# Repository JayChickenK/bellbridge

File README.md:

# BellBridge

**An isolated ESP32-C6 board that brings a Ritto 7630 TwinBus apartment intercom into Home Assistant.**

BellBridge connects to four terminals of the indoor station. It tells the
**apartment bell** from the **street bell** and can **open the street door**, all
locally through [ESPHome](https://esphome.io/) with no cloud involved. It is the circuit of
[duramson/ritto-esp](https://github.com/duramson/ritto-esp) turned into a
27.5 × 22.8 mm board that PCBWay assembles completely, ESP32-C6 module included.

<!-- TODO after testing: replace the status line, e.g.
> **Status:** v2.0 built and tested on a Ritto 7630 (YYYY-MM-DD), see the [test report](docs/testing.md).
-->
> [!WARNING]
> **Status:** hardware v2.0 is designed and checked, but it has not yet been built or
> tested on an intercom. It is v1.15 turned for mounting in the Ritto 7630: antenna up,
> USB-C and the screw terminal side by side on the bottom edge, with smaller parts (TLP293
> optocouplers, 0402 resistors and capacitors). Same circuit and GPIOs; see the
> [changelog](CHANGELOG.md).

<!-- TODO: add photos, e.g.

-->

The assembled board as a KiCad render, looking at its bottom edge: USB-C and the screw
terminal side by side in front, the module behind them with its antenna sticking out
5.2 mm past the far (top) edge.
The USB-C receptacle and the screw terminal are simplified models drawn to their
datasheet dimensions; the other parts use the 3D models from KiCad's and Espressif's
libraries.

| Top (render) | Bottom (render) |
| --- | --- |
|  |  |

These two renders show the bare board, pads and silkscreen without the parts.

## Features

- **Two bells told apart:** the chime line pulses on every ring, and the floor line drops
  only on an apartment ring. The firmware combines the two into "Doorbell Main" and
  "Doorbell Apartment".
- **Door opener:** an "Open Door" button in Home Assistant pulls the opener line to bus
  ground for 0.5 s (adjustable). An optional "Auto Open" switch lets every street ring
  open the door while it is on, for expected guests; it turns itself off after an
  adjustable time (30 minutes by default) and on every restart.
- **Galvanic isolation:** all three lines go through optocouplers. Bus ground and USB
  ground are kept apart by a 1.6 mm copper-free strip on both layers.
- **Powered from USB-C (5 V), not from the bus.** USB ESD protection right in the D+/D−
  path, 3.3 V LDO.
- **ESP32-C6-MINI-1-N4:** Wi-Fi 6 with a PCB antenna, an encrypted Home Assistant API,
  password-protected OTA updates, and diagnostics (signal, uptime, chip temperature, IP
  address).
- **Fully assembled by PCBWay.** The screw terminal is the only through-hole part.
- **Drop-in for ritto-esp:** same terminal order, same ESPHome node and entity names,
  so existing automations keep working.

## How it works

The Ritto 7630 shares one two-wire TwinBus with both door stations and all flats.
[ritto-esp](https://github.com/duramson/ritto-esp#reverse-engineering-the-bus) measured the
board with an oscilloscope:

| Ritto terminal | Signal | Behaviour |
| --- | --- | --- |
| 2 KLINGEL (chime) | input | about 5 V for ~500 ms on **any** ring |
| 4 ETAGE (floor) | input | idles at about 5 V, **drops to ground** while the apartment button is pressed |
| 5 door opener | output | buzzes the street door when **pulled to ground** |
| 1 / 6 GND | ground | bus ground |
| 3 +24 V | — | bus supply, **never connected to BellBridge** |

A falling ETAGE line means "apartment bell". The chime pulse that follows about 1.6 s later
is blocked for a few seconds, so a chime pulse on its own means "street door".

## Hardware at a glance

| | |
| --- | --- |
| Size | 27.5 × 22.8 mm, 2 layers, 1.6 mm, no mounting holes; 27.5 × 28.0 mm with the module's antenna, which sticks out past the top edge |
| Connectors | USB-C and the screw terminal side by side on the bottom edge; both cables leave downward |
| Tallest part | screw terminal J1, 8.4 mm; then the USB-C receptacle, 3.3 mm, and the module, 2.4 mm |
| Controller | Espressif ESP32-C6-MINI-1-N4 (4 MB flash, PCB antenna) |
| Power | USB-C, 5 V; AP2112K-3.3 LDO; USBLC6-2P6 ESD protection |
| Inputs | CHIME and FLOOR, 1.5 kΩ / 0.5 W into TLP293 optocouplers (about 2.5 mA at 5 V) |
| Output | DOOR, TLP293 transistor to bus ground |
| Isolation | separate grounds, 1.6 mm copper-free barrier, 5.1 mm between the optocouplers' input and output pads, 3,750 V<sub>rms</sub> optocouplers |
| Terminal | DORABO DB125-2.54, 4 pins at 2.54 mm: DOOR, CHIME, FLOOR, GND |

Details, the parts list and the design checks are in [hardware/README.md](hardware/README.md).

## Versions

| | v2.0 (current) | [v1.15](https://github.com/JayChickenK/bellbridge/tree/v1.15), [v1.14](https://github.com/JayChickenK/bellbridge/tree/v1.14), [v1.13](https://github.com/JayChickenK/bellbridge/tree/v1.13), [v1.12](https://github.com/JayChickenK/bellbridge/tree/v1.12) and [v1.1](https://github.com/JayChickenK/bellbridge/tree/v1.1) | [v1.0](https://github.com/JayChickenK/bellbridge/tree/v1.0) |
| --- | --- | --- | --- |
| Board | 27.5 × 22.8 mm; 28.0 mm tall with the antenna | 26.2 × 27.5 mm; 31.4 mm wide with the antenna | 36.4 × 31.5 mm |
| Antenna | past the top edge, as Espressif recommends | past the left edge, as Espressif recommends | on the board, at its edge |
| USB-C | bottom edge, beside the terminal; HRO's recommended land | top edge, HRO's recommended land | left edge, KiCad's land |
| Terminal | bottom edge, wires leave downward; DORABO, 2.54 mm, 26–18 AWG | right edge; DORABO, 2.54 mm, 26–18 AWG | KANGNEX, 3.81 mm, 26–16 AWG |
| USB ESD array | USBLC6-2P6 in the D+/D− path | USBLC6-2P6 in the D+/D− path | USBLC6-2SC6 on side branches |
| Optocouplers | TLP293 (SO4, 1.27 mm pitch) | LTV-357T (SO-4) | LTV-817S (SMDIP-4) with a milled slot |
| Passives | 0402, the 10/22 µF capacitors 0603; R2/R3 in 0805, 0.5 W | 0603; R2/R3 in 1210, 0.5 W | 0805; R2/R3 in 2512, 1 W |
| Download mode, reset | test pads on the back, replug USB | test pads on the back, replug USB | BOOT and RESET buttons |

v1.12 is v1.1 with three part values changed (R6 10 kΩ, C6 10 µF, C2 22 µF) and a wider
panel note for PCBWay; the copper is the same. v1.13 adds tracks for the bus ground, so it no
longer depends on the ground pour alone; v1.14 prints the terminal labels with thicker
lines, and v1.15 has smoother tracks, redrawn by hand in KiCad. v2.0 turns the layout for
mounting in the Ritto 7630, with both cables leaving at the bottom, and uses smaller parts
(TLP293 optocouplers, 0402 resistors and capacitors). All versions have the
same circuit,
terminal order and GPIOs. v1.0 has been assembled (photos below); the later versions have
not been built yet. The firmware in this branch runs on
all of them; the copy in the v1.0 files has a bell-logic bug (see the
[changelog](CHANGELOG.md)). Each version's order files are attached to its
[release](https://github.com/JayChickenK/bellbridge/releases).

| BellBridge v1.0, assembled | BellBridge v1.0, assembled (angled view) |
| --- | --- |
|  |  |

## Wiring

| BellBridge J1 | Ritto 7630 terminal |
| --- | --- |
| DOOR | 5 (door opener) |
| CHIME | 2 (KLINGEL) |
| FLOOR | 4 (ETAGE) |
| GND | 1 or 6 (GND) |
| — | 3 (+24 V) stays unconnected |

See [docs/installation.md](docs/installation.md) before you open the intercom.

## Getting started

1. **Order** the assembled board: [docs/ordering.md](docs/ordering.md).
2. **Flash** the firmware over USB-C: [firmware/README.md](firmware/README.md).
3. **Test** it on the bench: [docs/testing.md](docs/testing.md).
4. **Install** it at the intercom: [docs/installation.md](docs/installation.md).
5. **Automate** in Home Assistant. The
   [ritto-esp automations](https://github.com/duramson/ritto-esp/tree/main/home-assistant)
   (notifications, parcel mode, personal door webhooks) work unchanged.

## Test results

<!-- TODO after testing: fill in from docs/testing.md -->

| Test | Result |
| --- | --- |
| Assembly inspection, isolation, 3.3 V rail | not yet tested |
| Flashing over USB-C, Wi-Fi signal | not yet tested |
| Bench test of CHIME, FLOOR and DOOR | not yet tested |
| Street bell, apartment bell, door opener on a Ritto 7630 | not yet tested |
| Long-term run without false triggers | not yet tested |

## Repository layout

```
hardware/    board generator (generate.py), KiCad board, BOM, CPL, PCBWay order files
firmware/    ESPHome configuration and secrets template
docs/        ordering, installation and test guides, images
```

## Credits

- [duramson/ritto-esp](https://github.com/duramson/ritto-esp): reverse engineering of the
  7630, the circuit and the ESPHome firmware this board is built on (MIT License).
- [deh0511.de TwinBus](https://deh0511.de/twinbus/) and
  [quhfan.de](https://quhfan.de/post/ritto-twinbus-7630-smart-home-assistant/): terminal
  pinout of the 7630.

## License

[MIT](LICENSE). The firmware is derived from ritto-esp, whose MIT notice is kept in
[LICENSE](LICENSE) and in the firmware file.

Ritto and TwinBus are trademarks of their respective owners. This project is not
affiliated with or endorsed by them. You build and install it at your own risk. In a rented
flat, the intercom usually belongs to the building, so ask before you modify it.

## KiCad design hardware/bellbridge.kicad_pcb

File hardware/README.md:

# BellBridge hardware (v2.0)

[`generate.py`](generate.py) places and routes every part, checks the result, and writes the
KiCad board and the PCBWay order files. For v2.0 the tracks of every net but VBUS were routed
by `generate.py` and then smoothed in the style of the tracks redrawn by hand for v1.15
(45° corners, no stair steps); [`hand_routes.json`](hand_routes.json) holds them, and
`generate.py` lays them down instead of its own routes for those nets. To change the board,
change the script or `hand_routes.json` and run it again (see [Regenerating](#regenerating));
edits made only in KiCad are overwritten by the next run.

## Overview

- **27.5 × 22.8 mm** board, 2 layers, 1.6 mm FR-4, no mounting holes; with the module's
  antenna sticking out past the top edge, 27.5 × 28.0 mm overall. Laid out for mounting in
  the Ritto 7630: antenna up, both cables leave at the bottom. v1.15 was 26.2 × 27.5 mm
  with the antenna to the left, v1.0 36.4 × 31.5 mm; [CHANGELOG.md](../CHANGELOG.md) lists
  what changed.
- **ESP32-C6-MINI-1-N4** module with PCB antenna, soldered by the assembler (not a plug-in
  XIAO board). It stands upright: its antenna sticks out 5.2 mm past the top edge.
- **USB-C** at the bottom edge, below the module, opening downward. As in HRO's drawing, the
  receptacle front sits 0.46 mm past the board edge.
- **Screw terminal J1** at the bottom edge, right of USB-C. Its wire openings face downward
  and the body overhangs the edge by 0.9 mm. At 8.4 mm, J1 is the tallest part; the module
  is about 2.4 mm.
- **Two grounds:** `GND_MCU` (USB, module) and `GND_BUS` (intercom) are never joined. An
  L-shaped 1.6 mm copper-free barrier on both layers separates all copper of the two sides,
  ground pours included. The optocouplers stand across it.
- **+24 V is not connected.** There is no pad and no net for it.

```
USB-C ─ USBLC6-2P6 ─ ESP32-C6-MINI-1        D+/D− run through U3 to the module
  └─ VBUS ─ AP2112K-3.3 ─ 3V3 ┘
                                     │ GPIO19     │ GPIO18     │ GPIO20
                                    OK1 (LED)    OK2 (photo)  OK3 (photo)
 GND_MCU   ════════════════ isolation barrier, 1.6 mm ═════════════════
 GND_BUS                            OK1 (photo)  OK2 (LED)    OK3 (LED)
                                     │            │ 1.5 kΩ     │ 1.5 kΩ
                                    DOOR         CHIME        FLOOR       GND
                                    └──────── J1, to the Ritto 7630 ────────┘
```

## Signals

| J1, right to left (top view) | Function | Direction | Module GPIO |
| --- | --- | --- | --- |
| DOOR | door opener (Ritto terminal 5) | output, OK1 pulls it to `GND_BUS` | GPIO19 |
| CHIME | chime, any ring (Ritto terminal 2, KLINGEL) | input | GPIO18 |
| FLOOR | apartment bell (Ritto terminal 4, ETAGE) | input | GPIO20 |
| GND | bus ground (Ritto terminal 1 or 6) | — | — |

**Inputs (OK2, OK3).** The LED sits on the bus side behind 1.5 kΩ. ritto-esp measured CHIME
and FLOOR at about 5 V (the scope traces top out around 4.8 V). That gives about 2.4 mA of
LED current, or 2.5 mA at a full 5 V. The 10 kΩ pull-ups (R4, R5) need 0.33 mA, far less
than the transistor sinks at that LED current: the TLP293's rank GB guarantees a CTR of
100–600 % at 0.5 mA as well as at 5 mA (Toshiba datasheet, table 8.1). The 1.5 kΩ resistors
(R2, R3) are Panasonic ERJ-P06F1501V, anti-surge thick-film parts in 0805 rated 0.5 W at
70 °C (derated linearly to zero at 155 °C; 27 V continuous at 1.5 kΩ), because Ritto
terminal 3 (+24 V) sits between KLINGEL and ETAGE. If a wire lands there by mistake, 15 mA
flows and each resistor takes 22.8 V and dissipates about 0.35 W, which the derating curve
allows up to about 95 °C ambient. A standard 0805 resistor (0.125 W) would not survive
that; KOA's SG73P2ATTD1501F (0805, rated 0.75 W at 70 °C) may replace the Panasonic part.
This covers a CHIME or FLOOR wire on +24 V, not the GND wire: with J1's GND on +24 V, the
LEDs of OK2 and OK3 would be driven backward (rated 5 V) and OK1's output from emitter to
collector (rated 7 V).

**Output (OK1).** GPIO19 drives the LED through 150 Ω (about 12 mA). The collector is on
DOOR and the emitter on `GND_BUS`, so the transistor pulls the opener line to bus ground.
The TLP293 is rated V<sub>CEO</sub> 80 V and 50 mA collector current. Rank GB guarantees 100
% CTR at I<sub>F</sub> = 5 mA, and Toshiba's CTR curve stays flat up to about 20 mA, so the
output sinks about 12 mA or more, typically about 24 mA (the LTV-357T-C of earlier versions:
rank C, 200 % at 5 mA, about 19 mA at 220 Ω). R6 (10 kΩ to ground) holds GPIO19 low from
reset until the firmware drives it, so the door does not buzz while the module boots. Only
while the chip itself is held in reset is the pin's weak internal pull-up on (ESP32-C6 IO
MUX table, GPIO19 = SDIO_CLK); against 10 kΩ it lifts the pin to only about 0.6 V, below the
LED's forward voltage, so OK1 stays off. While the firmware switches the LED on (12 mA), R6
draws another 0.33 mA.

**Straps and test pads.** GPIO8 and GPIO9 are strapping pins. GPIO8 has a 10 kΩ pull-up
(R12); GPIO9 relies on the module's internal pull-up, as in the MINI-1 datasheet's
peripheral schematic (figure 7: GPIO9 only goes to a jumper to ground). Espressif's chip
design guide recommends an external pull-up on GPIO9; one would not fit beside the module's
GPIO9 pin in the v1.1 layout, and v2.0 keeps the circuit. There are no buttons: `esptool`
puts the module into download mode over the USB serial/JTAG port, and replugging USB resets
it. If a broken firmware stops that from working, bridge the two bare pads on the back, TP1
(BOOT, GPIO9) and TP2 (GND), with tweezers while you plug in USB; the module then starts in
download mode. The test pads sit on the back, under the module's lower right corner near its
GPIO9 pin. No 3V3 or VBUS copper comes within 1 mm of them (3V3 is 1.3 mm from TP2), so a
slip of the tweezers cannot short the supply to ground; the nearest other copper is GPIO18's
tented via, 0.7 mm from TP1, an input that a slip cannot harm. EN has 10 kΩ (R8) and
10 µF (C6, the same part as C1 and C3), which holds the chip in reset for about 0.1 s after
power-up; Espressif gives 10 kΩ + 1 µF as values to adjust to the power-up timing. Pin 8 is
on the module's left side, right beside R8 and C6, so EN reaches them over 2.4 and 3.6 mm of
track on the front, without a via. GPIO15 stays open.

**Firmware.** The firmware uses the three GPIOs directly. The XIAO ESP32-C6 antenna switch
(GPIO3, GPIO14) does not exist here, so do not use the `seeed_xiao_esp32c6` board profile;
see [../firmware](../firmware/).

## Power

USB-C only, 5 V, with all four VBUS contacts connected. CC1 and CC2 each have 5.1 kΩ to
ground (R7, R10); SBU1/SBU2 stay open.

U3 (USBLC6-2P6) sits in the D+/D− path between the receptacle and the module, 2.7–5.2 mm
of track from the receptacle's pads and 2.2–3.0 mm from the module's pins (distances in
this section run along the copper from pad centre to pad centre). D+ runs through U3's
pin 1, and D− taps pin 4 with a 0.6 mm stub. Both lines stay on the front and run straight
up into the module's pins 18 and 17, 5.6–8.1 mm from the receptacle's pads, so a discharge
into the receptacle meets U3 before it reaches the module. U3's ground pin has its own via
0.85 mm away. Its VBUS pin and C7 (100 nF to ground) sit on one line, 1.65 mm apart, as in
the layout figure of ST's USBLC6-2 datasheet; VBUS arrives through a via between the two,
and C7's ground pad shares the via under module pin 14 (1.3 mm of track). CC1 runs from
its receptacle pad to R7 on the front, below C7, without a via.

The AP2112K-3.3 (600 mA, stable with ceramic capacitors) makes 3.3 V; its EN is tied to
VBUS. Capacitors: 10 µF + 100 nF at the input (C1, C4; 3.2 mm and 2.4 mm of track from
VIN), 10 µF at the output (C3, 3.0 mm from VOUT), and 100 nF + 22 µF at module pin 3 (C5,
C2; 2.5 mm and 4.2 mm from the pin, in the column along the left edge). VBUS runs as 0.5 mm
tracks from both pairs of receptacle VBUS pads to the regulator: the left pair on the
front, the right pair through a via and 4.8 mm on the back. On the front it passes C1 and
C4 on its way into VIN. The regulator's EN pin and the branch up to the via beside C7 are
0.4 mm (on into C7 as well), the last piece into U3's VBUS pin 0.3 mm. The 3V3 trunk runs
at 0.45 mm from VOUT up the left edge, beside the capacitor column, with 0.4 mm stubs into
C3, R8 and C5; from C5, 0.4 mm tracks go into pin 3 and on to C2. The feeds to the pull-up
resistors are 0.3 mm: R12's from the trunk at C3, on the back along the module's lower edge;
R4's and R5's from module pin 3, on the back across the module's upper half, clear of the
test pads.

The module draws up to 382 mA while it transmits (802.11b at 20.5 dBm, Espressif's
datasheet), and Espressif asks for a supply of at least 0.5 A; the AP2112K delivers
600 mA. Pin 3 has 22 µF + 100 nF, as in Espressif's reference circuit, another 10 µF sits
at the regulator output, and the module has its own decoupling under the shield. At 5 V in
and about 100 mA on average, the regulator
dissipates about 0.17 W, roughly 30 °C above ambient in SOT-23-5 (184 °C/W). Wi-Fi
transmits in short bursts, and the AP2112K limits its current and shuts down when
overheated.

Espressif's design guide also suggests footprints for 22–33 Ω series resistors and
capacitors to ground on D+/D− near the module, unpopulated at first. They are left out:
the USB serial/JTAG port is full-speed (12 Mbit/s), where neither these parts nor the
guide's 90 Ω differential impedance (not reachable on a 1.6 mm two-layer board) matter
over 10 mm of line. UART0 is not brought out
either; the guide wants it for Espressif's RF test firmware, while BellBridge loads its
firmware over USB, with TP1/TP2 forcing download mode.

## Layout rules

- **Isolation:** the barrier line is an L. It runs from the top edge down through the
  optocouplers, 23.2 mm from the left edge, to 10.85 mm above the bottom edge (just below
  the module), crosses above the input resistors R2 and R3 to 15.7 mm from the left edge,
  and runs down to the bottom edge between USB-C and the terminal. All copper of either
  ground domain keeps 0.8 mm from this line on both layers, so the two domains are at
  least 1.6 mm apart. Each optocoupler has 5.1 mm of bare board between its LED and
  transistor pads; the closest pads of the two sides are 2.4 mm apart, a USB-C shell lug
  and J1's GND pin at the bottom edge (v1.15: 4.3 mm, across the optocouplers). GPIO18
  leaves the module through a via beside its pin and runs on the back to R4 and OK2, so no
  track passes under the module's corner and the step can sit right below the module. The
  TLP293 is rated 3,750 V<sub>rms</sub> input to output, with 5.0 mm creepage and
  clearance. There is no milled slot. Both sides are low voltage (5 V USB, 24 V bus), so
  this is functional isolation, not mains safety isolation. `generate.py` checks pads,
  tracks, vias and the ground pour outlines on every run.
- **Bus side:** drawn by `generate.py` rather than routed, so that no line crosses another.
  FLOOR and CHIME drop straight from R3 and R2 into J1 on the front. LED_FLOOR leaves OK3
  on the front, runs down a lane between the barrier and the optocouplers' bus pads and
  along the barrier step above R2 and R3, and enters R3 from above; LED_CHIME drops from
  OK2 into R2. On the back, the bus ground runs from vias beside OK3 and OK2 (OK1 joins OK2
  on the front) down the same lane, under the resistors through a via between R3 and R2,
  and down the barrier side into J1's GND pin, around the "GND ISOLATED" text; DOOR runs
  from a via beside OK1 down the right side into J1. Seven vias on the bus side, and every
  piece of the bus ground pour on the front has one of them.
- **Antenna:** Espressif's ESP32-C6 hardware design guidelines want the module's PCB
  antenna outside the base board, with the antenna's feed point close to the board edge,
  and metal in the housing at least 15 mm away from the antenna. The module stands
  upright, so the antenna section sticks out 5.2 mm past the top edge. The MINI-1's feed
  is at its pin-1 end (the two legs of the antenna in the module datasheet's drawing),
  here the left end of the antenna: the module's pin-1 side, pins 1–11, runs down the left
  side 3.2 mm from the left edge (v1.15: 2.0 mm from the bottom edge). The column beside
  it holds C5 and C2 for pin 3 and the EN network for pin 8. The guide gives no distance in
  mm. The board's top edge is 0.2 mm into the antenna section and 0.5 mm from the module's
  last pads. The antenna section is a KiCad rule area (`Antenna keep-out`, F.Cu and B.Cu:
  no tracks, vias, pads or pours). A row of ground vias along the module's antenna end
  (every 1.6 mm, between its ground pad row and its exposed pad) ties both ground layers
  together there, as the guide asks.
- **USB-C receptacle:** its steel bottom plate lies on the board (HRO's drawing: 6.28 mm
  back from the front face). No signal copper runs under it on the front and no signal via
  sits under it, only ground vias, so a scratch in the solder mask cannot short a line to
  the grounded shell. CC1 and CC2 leave their pads backward, away from the opening, and
  run on the front to R7 and R10. The D+ link between B6 and A6 has to cross in front of
  the pads, because the pins alternate D+, D−, D+, D− at 0.5 mm pitch and no via fits
  between them. It runs 0.2 mm in front of the pads, under the plastic rear part of the
  receptacle.
- **Chip parts:** KiCad's 0402 lands (R_0402_1005Metric, C_0402_1005Metric) for the
  resistors and the 100 nF capacitors, KiCad's 0603 land for the 10 µF and 22 µF capacitors,
  which keep more of their capacitance at 3.3–5 V in 0603 (X5R loses capacitance under DC
  bias), and KiCad's 0805 land (R_0805_2012Metric) for the 0.5 W input resistors R2/R3.
- **Thermal spokes:** the ground pads of the chip parts (C1–C7, R6, R7, R10) join the
  pours through 0.4 mm spokes instead of solid copper, so both ends of each part heat
  alike during reflow and the parts do not stand up (tombstoning). The module's and the
  ICs' ground pads stay solid.
- **Vias** keep at least 0.15 mm of copper-free mask to every SMD pad and are tented.
  Their holes keep 0.30 mm to the holes of J1 and the receptacle lugs. No via sits under
  silkscreen text. Vias may sit under the module (tented) but keep 0.15 mm of mask to its
  pads. Ground pads close together share one via: OK1's and OK2's LED-side ground pads
  and R6's, module pin 1 and C5, module pin 11 and C6, module pin 14 and C7; R10's ground
  pad runs straight into the USB-C receptacle's shell lug below it. 47 vias in all.
- **Test pads:** TP1 and TP2 get bridged with tweezers, so 3V3 and VBUS keep at least 1 mm
  from them (tracks on the back, vias on either layer); the router and `generate.py`'s
  checks hold every track to it.
- **Optocoupler land:** Toshiba's recommended land for the TLP293 (datasheet section 13):
  0.8 × 1.2 mm pads at 1.27 mm pitch, rows 6.3 mm apart. KiCad has no footprint for it;
  its `SOP-4_4.4x2.6mm_P1.27mm` has the same body (used for the 3D renders) but longer pads
  4.75 mm apart.
- **U3 land:** KiCad's `SOT-666` (outer pads 0.5 × 0.375 mm, centre pads 0.65 × 0.3 mm,
  1.2 mm between the pad columns). ST's datasheet suggests 0.30 × 0.99 mm pads with
  0.62 mm between the rows. Both cover the leads of the SOT-666 outline in ST's table 3;
  only KiCad's leaves room for D+ and D− between the pad columns.
- **J2 land:** HRO's recommended layout (TYPE-C-31-M-12 drawing, 2020-12-08). Signal pads
  0.30 and 0.60 mm wide run from 0.50 to 1.64 mm behind the line through the two 0.60 mm
  locating holes, which are 5.78 mm apart. The power and ground pads sit at ±2.40 and
  ±3.20 mm. KiCad's library footprint has 1.45 mm pads further back, the power and ground
  pads 0.05 mm further out, and 0.65 mm holes. The shell-lug slots follow HRO too:
  0.6 × 1.7 mm for the 1.10 mm lugs beside the pad row and 0.6 × 1.4 mm for the 0.80 mm
  lugs near the opening (KiCad's library: 1.2 mm), so every lug has 0.6 mm of play along
  its slot. The pads keep KiCad's 0.2 mm copper ring (1.0 × 2.1 and 1.0 × 1.8 mm; HRO:
  0.9 mm wide). HRO puts the hole line 5.79 mm from the board edge, so the receptacle
  front overhangs by 0.46 mm.

## Parts

All parts are on the top side. The BOM (`bom.csv`, the same table as `bom.xlsx`) uses the
columns of PCBWay's BOM quotation and has one line per part number. TP1 and
TP2 are bare copper pads on the back, not parts; they are left out of the BOM and CPL.

| Ref | Part | Manufacturer | MPN | LCSC |
| --- | --- | --- | --- | --- |
| U1 | ESP32-C6 module, 4 MB flash, PCB antenna | Espressif | ESP32-C6-MINI-1-N4 | C5736265 |
| U2 | LDO 3.3 V 600 mA, SOT-23-5 | Diodes Incorporated | AP2112K-3.3TRG1 | C51118 |
| U3 | USB ESD protection, 2 lines + VBUS, SOT-666 | STMicroelectronics | USBLC6-2P6 | C15999 |
| J1 | Screw terminal, 4 pins, 2.54 mm, 8.4 mm high | DORABO | DB125-2.54-4P-GN-S | C918122 |
| J2 | USB-C receptacle | HRO | TYPE-C-31-M-12 | C165948 |
| OK1–OK3 | Optocoupler, SO4, CTR rank GB (100–600 %), 80 V | Toshiba | TLP293(GB-TPL,E | C77656 |
| R1 | 150 Ω 1 % 62.5 mW 0402 | UNI-ROYAL | 0402WGF1500TCE | C25082 |
| R2, R3 | 1.5 kΩ 1 % 0.5 W 0805, anti-surge | Panasonic | ERJ-P06F1501V | C543553 |
| R4, R5, R6, R8, R12 | 10 kΩ 1 % 62.5 mW 0402 | UNI-ROYAL | 0402WGF1002TCE | C25744 |
| R7, R10 | 5.1 kΩ 1 % 62.5 mW 0402 | UNI-ROYAL | 0402WGF5101TCE | C25905 |
| C1, C3, C6 | 10 µF 10 V X5R 0603 | Samsung | CL10A106KP8NNNC | C19702 |
| C2 | 22 µF 6.3 V X5R 0603 | Samsung | CL10A226MQ8NRNC | C59461 |
| C4, C5, C7 | 100 nF 16 V X7R 0402 | Samsung | CL05B104KO5NNNC | C1525 |

Every part has its LCSC number in the BOM's "Vendor Part #" column, and its "Customer Reply"
column tells PCBWay per line what may be substituted: resistors and capacitors by parts of
the same value, size, rating and dielectric; R2/R3 must stay 0805 and at least 0.5 W (KOA
SG73P2ATTD1501F fits). Do not substitute U1, U3, OK1–OK3, J1 or J2 (J2's land follows HRO's
drawing).

J1's footprint, overhang, CPL centre and silkscreen follow the DORABO drawing
DB125-2.54-XXP-C-S (2022-04-06): pitch 2.54 mm, 0.50 × 0.85 mm pins in 1.20 mm holes
(2.0 mm pads), body 6.30 mm deep and 8.40 mm high, the pin row 3.10 mm from the wire face
and 3.20 mm from the back. Wires 26–18 AWG (1.0 mm²), stripped 4–5 mm, M1.6 screws at
most 0.1 N·m. Rated 150 V / 7 A (UL), −40 to +105 °C.

## Files

| File | Content |
| --- | --- |
| `generate.py` | the design: placement, routing, checks, all outputs |
| `hand_routes.json` | the tracks of every net but VBUS (v2.0: routed by `generate.py`, then smoothed), laid down by `generate.py` instead of its own routes; delete a net's entry when its pads move, so that `generate.py` routes it again |
| `bellbridge.kicad_pcb`, `bellbridge.kicad_pro` | KiCad board (ground pours are unfilled; press **B** in KiCad to fill them) |
| `bellbridge.kicad_sch` | schematic of the board with the same references, values, footprints and net names, so KiCad's ERC and its schematic-to-board check can run; `generate.py` does not write it, so update it by hand after a board change |
| `bom.csv`, `bom.xlsx` | bill of materials in the columns of PCBWay's BOM quotation: Item #, *Designator, *Qty, Manufacturer, *Mfg Part #, Description / Value, Vendor Part # (LCSC), *Package/Footprint, Mounting Type, Customer Reply (what may be substituted); the same table as text and as a spreadsheet |
| `cpl.csv` | placement: origin at the board's lower-left corner, mm, Y up, KiCad rotation; J1 at its body centre |
| `pcbway/` | Gerbers, drill files, job file, BOM, CPL, `PCBWAY-REMARKS.txt` and the order zip `bellbridge-v2.0-pcbway.zip` |
| `drc-report.json` | KiCad DRC report of the last run |
| `plots/` | quick previews from `generate.py` (net colours, both sides) |

## Regenerating

Requirements: Python 3.9 or later (tested with 3.11 and 3.13); Pillow (optional, only for
`plots/`); KiCad 10 for the Gerbers and the DRC (tested with 10.0.6 and 10.0.8). On Windows
`generate.py` finds a default KiCad 10 install; elsewhere `kicad-cli` must be on `PATH`.

```bash
cd hardware
python generate.py
```

The run takes well under a minute. It places all parts and routes them with a deterministic
router, then puts the tracks from `hand_routes.json` in place of the routes of those nets.
Then it runs its own checks: isolation barrier, clearances, antenna keep-out, J2's steel
plate and U1's ground pad, supply copper 1 mm from the test pads, via-to-pad and via-to-hole
distances and pin-1 marks. It writes
the board, BOM, CPL and previews. After that, `kicad-cli` exports Gerbers, drill and
position files and runs the DRC with refilled pours. `pcbway/` and the order zip are written
only when the DRC reports **0 violations and 0 unconnected items**. The output ends with:

```
python-drc 0
kicad-drc violations 0 unconnected 0 {}
zip .../pcbway/bellbridge-v2.0-pcbway.zip
```

## Design verification (v2.0)

v2.0 has the circuit and nets of v1.15 in a new layout, with Toshiba TLP293 optocouplers
(R1 150 Ω instead of 220 Ω), the 1.5 kΩ input resistors in 0805, the other resistors and the
100 nF capacitors in 0402, and every track new (see [CHANGELOG.md](../CHANGELOG.md)).

- `generate.py` checks for v2.0: 0 errors. KiCad 10.0.8 DRC with all severities and
  refilled pours: 0 violations, 0 unconnected items. KiCad's schematic-to-board check finds
  no difference in nets or parts; it only names the 27 unconnected pins differently.
- The nets rebuilt from the Gerber copper and the plated holes match the schematic's
  netlist (47 nets, 133 pins). Measured on the Gerbers: 0.20 mm smallest gap between nets,
  0.20 mm narrowest track, 0.175 mm via ring, 0.62 mm between holes, 0.475 mm copper to
  edge.
- Measured on the KiCad-filled board: the two grounds stay 1.60 mm apart on both layers,
  pours included, along the whole L-shaped barrier; no signal copper on the front under the
  USB-C shell's steel plate and no signal via under it; on the front, nothing but module
  ground within 1 mm of U1's ground pad; U3 in the D+/D− path; VBUS keeps a 0.5 mm path to
  the regulator and 3V3 a 0.4 mm path to the module; all 47 vias have copper on both
  layers.
- Track shapes: 139 tracks on 19 nets in `hand_routes.json`; against the router's output,
  1 right-angle bend (no 45° cut fits there) instead of 38, and no stair steps or hairpins
  (10 and 1); no leftover copper.
- 0402 parts: KiCad's library lands, checked against the KiCad 10 footprints; each CPL
  position sits on its part's pads with the rotation matching pin 1; LCSC lists all four
  part numbers (UNI-ROYAL 0402WGF1002TCE, 0402WGF5101TCE, 0402WGF1500TCE, Samsung
  CL05B104KO5NNNC) in stock. R1 dissipates about 22 mW of its 62.5 mW.
- R2/R3: KiCad's R_0805_2012Metric land; Panasonic ERJ-P06F1501V, 1 %, 0.5 W at 70 °C
  (derated to zero at 155 °C), 400 V limiting voltage, AEC-Q200; each CPL position sits on
  its part's pads with the rotation matching pin 1. LCSC lists it as C543553 but had none
  in stock on 2026-11-25 (nor the YAGEO 1210 part used before); PCBWay buys through its own
  channels, and KOA's SG73P2ATTD1501F (0805, rated 0.75 W at 70 °C) is allowed instead.
  LCSC had no Samsung CL10A106KP8NNNC (C1, C3, C6) in stock that day either; the BOM
  allows any 10 µF 10 V X5R 0603 in its place.
- Datasheet review before release, against the manufacturers' PDFs: the module's 53 pins,
  land, boot straps (GPIO8 pulled up, GPIO9 to TP1, GPIO15 ignored with unburnt eFuses) and
  peripheral circuit (Espressif MINI-1 datasheet v1.5, chip datasheet v1.6, hardware design
  guidelines: antenna placement, 10 µF and ESD at the power entry); AP2112K pinout and
  ratings (Diodes); USBLC6-2P6 pinout and SOT-666 land (ST); TLP293 pins, land and ratings
  (Toshiba Rev. 6.0); USB-C land against HRO's drawing (2020-12-08) and J1 against
  DORABO's (2022-04-06); ERJ-P06 and SG73P ratings (Panasonic, KOA); the part-number codes
  of the Samsung capacitors and UNI-ROYAL resistors; every LCSC number against its part.
  The firmware passes ESPHome 2026.11.0's configuration check.
- TLP293: land and pins (1 anode, 2 cathode, 3 emitter, 4 collector) from Toshiba's
  datasheet (Rev. 6.0, 2019-11-29), checked in the board and against the CPL rotations; LCSC
  lists TLP293(GB-TPL,E with about 48,000 in stock. The schematic's symbol keeps KiCad's
  LTV-357T drawing (same pins), renamed to TLP293.
- Placement: J1's body clears a mated USB-C plug (overmold up to 12.35 mm wide) by
  0.5 mm; the antenna section is free of copper on both layers.

v1.15 keeps the parts, vias and copper pours of v1.14 and replaces 123 tracks on 17 nets with
98 smoother ones, redrawn by hand in KiCad (`hand_routes.json`). VBUS keeps its v1.14 routing.

- `generate.py` checks for v1.15: 0 errors, with clearances now measured against the pads'
  real outline (rounded corners, oval ends), and the keep-outs of J2's steel plate and U1's
  ground pad checked for hand-drawn tracks too. KiCad 10.0.8 DRC with all severities and
  refilled pours: 0 violations, 0 unconnected items; the schematic-to-board check finds no
  difference in nets or parts.
- Track shapes on the 17 redrawn nets (v1.14 in brackets): 21 % of the track length at 45°
  (2 %), 4 right-angle corners (52), no stair steps (11), 4 pieces under 0.3 mm (35), 234 mm
  of track (243); no leftover copper.
- The nets rebuilt from the Gerber copper and the plated holes match the schematic's
  netlist (47 nets, 133 pins). The isolation between the two grounds stays at 1.60 mm on
  both layers, pours included; no signal copper lies under the USB-C shell's steel plate; U3
  stays in the D+/D− path; VBUS keeps a 0.5 mm path to the regulator and 3V3 a 0.4 mm path to
  the module; every via has copper on both layers. Measured on the Gerbers: 0.20 mm smallest
  gap between nets, 0.175 mm via ring, 0.475 mm copper to edge.

v1.14 changes only the silkscreen: J1's labels are 0.6 mm wide instead of 0.55 mm, so KiCad
plots them with 0.15 mm lines (it caps a text's stroke at a quarter of its character size,
which gave 0.138 mm). Regenerated, its copper, solder mask, paste, outline and drill files,
BOM and CPL are the same as v1.13's (only dates and the KiCad version in the file headers
differ).

- `generate.py` checks for v1.14: 0 errors. KiCad 10.0.8 DRC with all severities and
  refilled pours: 0 violations, 0 unconnected items. KiCad's schematic-to-board check finds
  no difference in nets or parts; it only names the 27 unconnected pins differently.
- An independent check that starts from the order files alone: the nets rebuilt from the
  Gerber copper and the plated holes match the schematic's netlist (47 nets, 133 pins).
  Measured on the Gerbers: 0.20 mm smallest gap between nets, 0.20 mm narrowest track,
  0.175 mm via ring, 0.36 mm between holes, 0.475 mm copper to edge, 0.10 mm narrowest
  mask web; every silkscreen line at least 0.15 mm (the arrows are filled shapes); paste
  only on pads; each CPL position on its part's pads, with the rotation matching pin 1.

v1.13 routes the bus ground (`GND_BUS`) with tracks between OK1, OK2, OK3 and J1: with the bus
ground pour removed as a test, every bus-ground pad stays connected (v1.12: 6 connections
missing). All other nets and every part are unchanged from v1.12.

- `generate.py` checks for v1.13: 0 errors. KiCad 10.0.6 DRC with all severities and
  refilled pours: 0 violations, 0 unconnected items.

v1.12 changes three part values, the PCBWay panel note and the version on the back
silkscreen. Regenerated, its copper, solder mask, paste, outline and drill files and the CPL
are the same as v1.1's (only the revision and date attributes in the file headers differ),
so the v1.1 checks below still hold.

- `generate.py` checks for v1.12: 0 errors. KiCad 10.0.6 DRC with all severities and
  refilled pours: 0 violations, 0 unconnected items.
- The new 22 µF capacitor (Samsung CL10A226MQ8NRNC, LCSC C59461) uses the same 0603 land
  as the other capacitors; LCSC lists it as 22 µF ±20 %, 6.3 V, X5R.

Done for v1.1 before ordering:

- `generate.py` checks: 0 errors. KiCad 10.0.6 DRC with all severities and refilled
  pours: 0 violations, 0 unconnected items.
- An independent review of the KiCad-filled board (pcbnew geometry), 70 checks: outline,
  the turned module (antenna past the left edge with 2.6 of its 71 mm² over the board,
  feed end 2.0 mm from the bottom edge, pads 0.5 mm from the edge), no copper under the
  antenna on either layer and the KiCad rule area there, the ground vias along the
  antenna end, pin and optocoupler nets, isolation of at least 1.6 mm on both layers
  including pours, J2 against HRO's drawing, power path widths, decoupling distances, U3
  in the D+/D− path with C7 at its VBUS pin, no signal copper under the USB-C shell, thermal
  spokes on the 0603 ground pads, two VBUS vias, via distances to pads and holes, pin-1 dots,
  J1 orientation, labels and arrows, the test pads, silkscreen, and BOM/CPL against the
  board (the BOM in PCBWay's quotation columns, CSV and XLSX alike).
- Every footprint except J1 compared pad by pad with the KiCad 10 library, and U1 also with
  Espressif's own KiCad footprint: same copper. The exceptions are J2's signal pads,
  locating holes and the two shell-lug slots near the opening, which follow HRO's drawing
  on purpose (see Layout rules).
- Part fit: every part's datasheet body at maximum size lies inside its courtyard, and
  no two parts come closer than 0.45 mm (pads and bodies; J1 to R3 0.6 mm). A mated USB-C
  plug (overmold up to 12.35 × 6.5 mm) clears the board and every part. J1 (8.4 mm) is the
  tallest part, then J2 (3.3 mm) and the module (2.4 mm).
- Every part checked against its manufacturer's datasheet (Espressif, Diodes, ST, HRO,
  DORABO, Lite-On, YAGEO, UNI-ROYAL, Samsung): pinout, land pattern, ratings and the
  part-number coding of value, tolerance, voltage and dielectric.
- Pin functions of U1, U2, U3 and OK1–OK3 compared with KiCad's symbols. KiCad's
  LTV-357T symbol has unnamed pins; the board follows Lite-On's 1 anode, 2 cathode,
  3 emitter, 4 collector.
- Firmware: the GPIOs are the same as on v1.0. Compiled with ESPHome 2026.11.0 for the
  ESP32-C6, with only ESPHome's note on the OTA password as a warning; not yet flashed
  (see [../firmware/README.md](../firmware/README.md)).

Still open: the built board. See [../docs/testing.md](../docs/testing.md).

## Differences from ritto-esp

Same circuit as the ritto-esp perfboard build: same terminal order (door opener, chime,
floor, ground), same polarity, the same GPIOs (XIAO D8 = GPIO19, D9 = GPIO20, D10 = GPIO18),
a resistor in front of the door-opener LED (150 Ω here, 220 Ω there), and an isolated bus
side. Differences:

- 1.5 kΩ input resistors instead of 680 Ω: 2.4 mA instead of about 5 mA, and the CHIME
  and FLOOR inputs survive their wire landing on +24 V (not the GND wire, see Signals).
- External 10 kΩ pull-ups on GPIO18 and GPIO20; `pullup: true` in the firmware does no harm.
- 10 kΩ from GPIO19 to ground, so the opener stays off during boot.
- TLP293 (CTR rank GB, SO4) instead of a PC817.
- ESP32-C6-MINI-1-N4 module instead of a XIAO ESP32-C6, plus USB ESD protection.

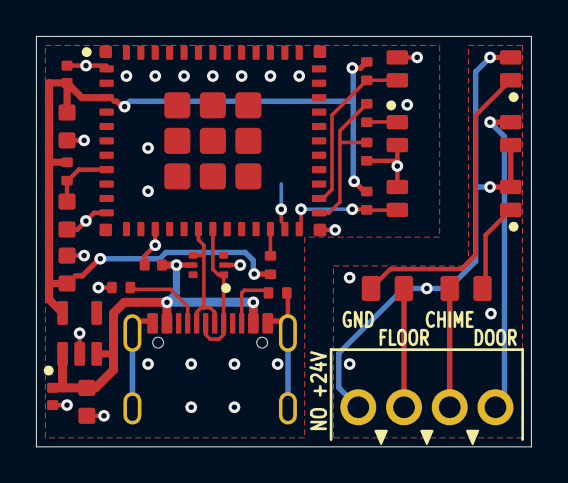
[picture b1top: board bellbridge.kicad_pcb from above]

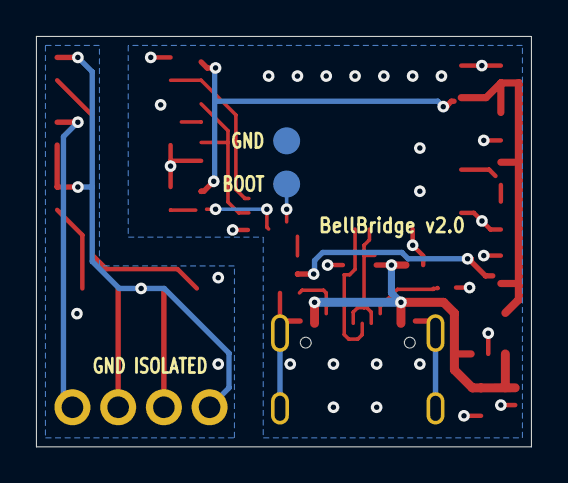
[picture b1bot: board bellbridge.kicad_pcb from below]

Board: 2 copper layers, 27.5 x 22.8 mm, 27 parts (2 on the bottom side), 20 nets.

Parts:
C1, C3, C6: 10uF; C_0603
C2: 22uF; C_0603
C4, C5, C7: 100nF; C_0402
J1: 2.54mm 4P; TerminalBlock_DORABO_DB125-2.54_1x04_P2.54mm
J2: USB-C; USB_C_HRO_TYPE-C-31-M-12
OK1, OK2, OK3: TLP293; Toshiba_SO4_TLP293
R1: 150; R_0402
R2, R3: 1.5k 0.5W; R_0805
R4, R5, R6, R8, R12: 10k; R_0402
R7, R10: 5.1k; R_0402
TP1: BOOT; TestPoint_Pad_D1.5mm
TP2: GND; TestPoint_Pad_D1.5mm
U1: ESP32-C6-MINI-1-N4; ESP32-C6-MINI-1
U2: AP2112K-3.3; SOT-23-5
U3: USBLC6-2P6; SOT-666

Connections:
3V3: C2.1, C3.1, C5.1, R4.2, R5.2, R8.2, R12.2, U1.3, U2.5
CC1: J2.A5, R7.2
CC2: J2.B5, R10.2
CHIME: J1.2, R2.2
DOOR: J1.1, OK1.4
EN: C6.1, R8.1, U1.8
FLOOR: J1.3, R3.2
GND_BUS: J1.4, OK1.3, OK2.2, OK3.2
GND_MCU: C1.1, C2.2, C3.2, C4.1, C5.2, C6.2, C7.2, J2.A1, J2.A12, J2.B1, J2.B12, J2.SH, OK1.2, OK2.3, OK3.3, R6.1, R7.1, R10.1, TP2.1, U1.1, U1.2, U1.11, U1.14, U1.36, U1.37, U1.38, U1.39, U1.40, U1.41, U1.42, U1.43, U1.44, U1.45, U1.46, U1.47, U1.48, U1.49, U1.50, U1.51, U1.52, U1.53, U2.2, U3.2
GPIO8: R12.1, U1.22
GPIO9: TP1.1, U1.23
GPIO18: OK2.4, R4.1, U1.24
GPIO19: R1.1, R6.2, U1.25
GPIO20: OK3.4, R5.1, U1.26
LED_CHIME: OK2.1, R2.1
LED_DOOR: OK1.1, R1.2
LED_FLOOR: OK3.1, R3.1
USB_DM: J2.A7, J2.B7, U1.17, U3.4
USB_DP: J2.A6, J2.B6, U1.18, U3.1
VBUS: C1.2, C4.2, C7.1, J2.A4, J2.A9, J2.B4, J2.B9, U2.1, U2.3, U3.5

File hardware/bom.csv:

Item #,*Designator,*Qty,Manufacturer,*Mfg Part #,Description / Value,Vendor Part #,*Package/Footprint,Mounting Type,Customer Reply
1,U1,1,Espressif,ESP32-C6-MINI-1-N4,"ESP32-C6 module, 4 MB flash, PCB antenna",C5736265,ESP32-C6-MINI-1,SMD,No substitute
2,U2,1,Diodes Incorporated,AP2112K-3.3TRG1,LDO 3.3 V 600 mA,C51118,SOT-23-5,SMD,
3,U3,1,STMicroelectronics,USBLC6-2P6,"USB ESD protection, 2 lines + VBUS, SOT-666",C15999,SOT-666,SMD,No substitute
4,J1,1,DORABO,DB125-2.54-4P-GN-S,"Screw terminal, 4 pins, pitch 2.54 mm, 8.4 mm high",C918122,TerminalBlock_DORABO_DB125-2.54_1x04_P2.54mm,THT,No substitute
5,J2,1,HRO,TYPE-C-31-M-12,"USB-C receptacle 16P, SMD with through-hole shell lugs",C165948,USB_C_HRO_TYPE-C-31-M-12,SMD,No substitute
6,"OK1, OK2, OK3",3,Toshiba,"TLP293(GB-TPL,E","Optocoupler SO4, transistor output, CTR rank GB (100-600 %), 80 V",C77656,Toshiba_SO4_TLP293,SMD,No substitute
7,R1,1,UNI-ROYAL,0402WGF1500TCE,Resistor 150 ohm 1 % 62.5 mW 0402,C25082,R_0402,SMD,"Equivalent OK: same value, size and rating"
8,"R2, R3",2,Panasonic,ERJ-P06F1501V,"Resistor 1.5 kohm 1 % 0.5 W 0805, anti-surge thick film",C543553,R_0805,SMD,"Alt. KOA SG73P2ATTD1501F; any 1.5k 0805, min. 0.5 W"
9,"R4, R5, R6, R8, R12",5,UNI-ROYAL,0402WGF1002TCE,Resistor 10 kohm 1 % 62.5 mW 0402,C25744,R_0402,SMD,"Equivalent OK: same value, size and rating"
10,"R7, R10",2,UNI-ROYAL,0402WGF5101TCE,Resistor 5.1 kohm 1 % 62.5 mW 0402,C25905,R_0402,SMD,"Equivalent OK: same value, size and rating"
11,"C1, C3, C6",3,Samsung,CL10A106KP8NNNC,Capacitor 10 uF 10 V X5R 0603,C19702,C_0603,SMD,"Equivalent OK: same value, size, voltage and dielectric"
12,C2,1,Samsung,CL10A226MQ8NRNC,Capacitor 22 uF 6.3 V X5R 0603,C59461,C_0603,SMD,"Equivalent OK: same value, size, voltage and dielectric"
13,"C4, C5, C7",3,Samsung,CL05B104KO5NNNC,Capacitor 100 nF 16 V X7R 0402,C1525,C_0402,SMD,"Equivalent OK: same value, size, voltage and dielectric"

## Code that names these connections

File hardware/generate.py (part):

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# converted to origin lower left / Y up in write_cpl(); render() draws the true top view.
# Derived from a larger 43.6 x 33.3 mm assembly board: no M3 holes, USB and the terminal moved,
# outline shrunk. The pre-release revisions were called KLEIN1..KLEIN3; KLEIN3 became v1.0.
# KLEIN2: USB-C turned to face the left edge, GPIO8 pull-up, AP2112K instead of AMS1117 and
# damper, one isolation barrier checked for all copper, nothing beside the antenna, button
# pads wired diagonally without tie tracks, 0.5 mm power paths, pin-1 dots placed and checked.
# KLEIN3: USB ESD array U3 (USBLC6-2SC6) above J2, CC pull-downs as 0603 beside it, J2 0.2 mm
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# regulator moved 0.4-0.5 mm left, the optocouplers and the terminal 1.0/0.8 mm, the
# optocoupler pitch went from 4.2 to 4.1 mm and the board's lower part moved up 0.4 mm.
# Optocouplers Toshiba TLP293 (SO4, 1.27 mm pitch, CTR rank GB) instead of the LTV-357T-C:
# the column is 3.6 mm pitch and ends higher, GPIO18 leaves the module through a via, the
# barrier step moved up to 17.15 mm and the board to 27.5 x 23.3 mm; R1 150 ohm.
# R2/R3 in 0805 (Panasonic ERJ-P06F1501V, 0.5 W anti-surge) instead of 1210: no via fits
# between their pads any more, so route() draws the bus side, and the board's lower part
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
# Terminal names, behind J1's body: the names are wider than the 2.54 mm pitch, so they stand
# centred over their pins in two staggered rows (row 0 next to the body).
J1_LABELS = (("DOOR", "1", 0), ("CHIME", "2", 1), ("FLOOR", "3", 0), ("GND", "4", 1))


def j1_label_at(pin, row):
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        8: "EN",
        17: "USB_DM",
        18: "USB_DP",
        22: "GPIO8",
        23: "GPIO9",
        24: "GPIO18",
        25: "GPIO19",
        26: "GPIO20",
    }
    pads = []
    # Left 1..11, bottom 12..24, right 25..35, top 36..48.
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def place_all():
    # 27.5 x 22.8 mm board (27.5 x 28.0 mm with the antenna). U1 at the top left, antenna up,
    # pins 1-11 (3V3, EN) down its left side, USB pins 17/18 in the middle of its lower side,
    # GPIO8/9/18 at its lower right, GPIO19/20 low on its right side. Left of the module a strip
    # with the pin-3 capacitors and the EN network, the 3V3 trunk between them and the module;
    # the regulator and its capacitors in the lower left corner. Under the module the ESD array
    # (right above the receptacle's USB pads), its VBUS capacitor, the GPIO8 pull-up and the CC
    # pull-downs; J2 at the bottom edge (front 0.46 mm past it). Right of the module a column of
    # resistors, then the optocouplers on the barrier (x = XB), from the top OK3 (GPIO20, FLOOR),
    # OK1 (GPIO19, DOOR), OK2 (GPIO18, CHIME): the module's GPIO20, GPIO19 and GPIO18 pins come
    # in that order, so their lines do not cross. Bus side: the optocouplers' right half, the
    # input resistors below the column and the terminal at the bottom edge beside J2, wire
    # openings down (front 0.9 mm past the edge).
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        "smd", "STMicroelectronics", "USBLC6-2P6", "C15999",
        (-1.5, -0.95, 1.5, 0.95),
    )
    # Optocouplers, 3.6 mm apart from the top: OK3 (GPIO20, FLOOR), OK1 (GPIO19, DOOR), OK2
    # (GPIO18, CHIME). Courtyard 0.25 mm around the 4.4 x 2.6 mm body and the pads.
    oc = (-4.0, -1.55, 4.0, 1.55)
    tosh = ("smd", "Toshiba", "TLP293(GB-TPL,E", "C77656", oc)
    y3 = round(BOARD_Y0 + 1.80, 3)
    y1, y2 = round(y3 + 3.60, 3), round(y3 + 7.20, 3)
    add_part("OK3", "TLP293", "Toshiba_SO4_TLP293", XB, y3, 180,
             opto_pads("LED_FLOOR", "GND_BUS", "GND_MCU", "GPIO20"), *tosh)
    add_part("OK1", "TLP293", "Toshiba_SO4_TLP293", XB, y1, 0,
             opto_pads("LED_DOOR", "GND_MCU", "GND_BUS", "DOOR"), *tosh)
    add_part("OK2", "TLP293", "Toshiba_SO4_TLP293", XB, y2, 180,
             opto_pads("LED_CHIME", "GND_BUS", "GND_MCU", "GPIO18"), *tosh)
    add_part(
        "J1", "2.54mm 4P", "TerminalBlock_DORABO_DB125-2.54_1x04_P2.54mm",
        25.50, round(BOARD_H - TB_FRONT + 0.90, 3), 180, terminal_pads(("DOOR", "CHIME", "FLOOR", "GND_BUS")),
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    r8 = (-1.68, -0.95, 1.68, 0.95)
    pan = ("smd", "Panasonic", "ERJ-P06F1501V", "C543553", r8)
    # Input resistors under the optocoupler column, each with its bus-side pad right above its
    # terminal pin, their pads 0.25 mm below the LED_FLOOR track that runs along the barrier
    # step (see route()). 0805 anti-surge thick film, 0.5 W at 70 C (see the hardware README).
    yr = round(YK + ISO_HALF + 1.25, 3)
    add_part("R3", "1.5k 0.5W", "R_0805", 19.50, yr, 0, r0805_pads("LED_FLOOR", "FLOOR"), *pan)
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    add_part("R7", "5.1k", "R_0402", round(j2x - 4.95, 3), 19.15, 0, r0402_pads("GND_MCU", "CC1"), "smd", uni, "0402WGF5101TCE", "C25905", r4)
    add_part("R10", "5.1k", "R_0402", round(j2x + 3.75, 3), 19.45, 180, r0402_pads("GND_MCU", "CC2"), "smd", uni, "0402WGF5101TCE", "C25905", r4)
    # Column between the module and the optocouplers, each part level with its optocoupler pin:
    # GPIO20 pull-up (OK3), LED resistor (OK1's anode), GPIO19 pull-down, GPIO18 pull-up (OK2).
    # R1 is 150 ohm: about 12 mA through OK1's LED, so the TLP293 (CTR rank GB, 100 % min.)
    # sinks at least as much on DOOR (typically twice that).
    # R6 is the pull-ups' 10k part: against the pin's weak pull-up (about 45k, on only while the
    # chip is held in reset) it keeps GPIO19 near 0.6 V, below the LED's forward voltage, and it
    # costs 0.33 mA while the LED is on.
    xr = round(XB - 4.85, 3)
    add_part("R5", "10k", "R_0402", xr, round(y3 + 0.125, 3), 90, r0402_pads("GPIO20", "3V3"), "smd", uni, "0402WGF1002TCE", "C25744", r4)
    add_part("R1", "150", "R_0402", xr, round(y1 - 1.145, 3), 270, r0402_pads("GPIO19", "LED_DOOR"), "smd", uni, "0402WGF1500TCE", "C25082", r4)
    add_part("R6", "10k", "R_0402", xr, round(y1 + 1.00, 3), 90, r0402_pads("GND_MCU", "GPIO19"), "smd", uni, "0402WGF1002TCE", "C25744", r4)
    add_part("R4", "10k", "R_0402", xr, round(y2 + 0.125, 3), 90, r0402_pads("GPIO18", "3V3"), "smd", uni, "0402WGF1002TCE", "C25744", r4)
    # GPIO8 pull-up under pin 22.
    add_part("R12", "10k", "R_0402", round(U1_X + 3.20, 3), 17.90, 270, r0402_pads("GPIO8", "3V3"), "smd", uni, "0402WGF1002TCE", "C25744", r4)
    # Column left of the module: 100 nF and 22 uF beside pin 3 (Espressif's reference values at
    # the 3V3 pin), then the EN network beside pin 8: 10k and 10 uF (C1's part), about 0.1 s of
    # reset delay; Espressif gives 10k + 1 uF as values to adjust to the power-up timing. The
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    # positive hit on D+/D- leaves through U3's upper diodes into VBUS. In line with U3's VBUS
    # pin, far enough left that the VBUS via fits between the two with 0.15 mm of mask to each.
    add_part("C7", "100nF", "C_0402", round(j2x - 3.155, 3), 17.90, 180, c0402_pads("VBUS", "GND_MCU"), "smd", sam, "CL05B104KO5NNNC", "C1525", c4)
    # Download-mode test pads on the back, under the module beside its GPIO9 pin: bridge BOOT to
    # GND while plugging in.
    tp = (-1.0, -1.0, 1.0, 1.0)
    add_part("TP1", "BOOT", "TestPoint_Pad_D1.5mm", round(U1_X + 3.80, 3), 13.40, 0, test_pad("GPIO9"), "board_only", "", "", "", tp)
    add_part("TP2", "GND", "TestPoint_Pad_D1.5mm", round(U1_X + 3.80, 3), 11.00, 0, test_pad("GND_MCU"), "board_only", "", "", "", tp)


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            seed_pad(q)

    # GPIO lines out of the module's lower right corner, drawn before the search so that they
    # fan out without crossing: GPIO20 (pin 26) up the inner lane beside the module to R5 and
    # on to OK3, GPIO19 (pin 25) up the outer lane to R6 and R1. GPIO18 (pin 24) is left to the
    # search: a track under the module's corner would hold the barrier step below it, so it
    # takes a via beside its pin and the back layer to R4 and OK2. OK1's LED joins R1 in the
    # search.
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    o3c = at("OK3", "4")
    xi, xo = round(U1_X + 6.62, 3), round(U1_X + 7.06, 3)
    d3 = round(o3c[1] - r5g[1], 3)
    add_poly("GPIO20", "F", [p26, (xi, p26[1]), (xi, r5g[1]), r5g, (round(o3c[0] - 1.0 - d3, 3), r5g[1]),
                             (round(o3c[0] - 1.0, 3), o3c[1]), o3c], 0.20)
    add_poly("GPIO19", "F", [p25, (xo, p25[1]), (xo, r1g[1]), r1g], 0.20)
    add_poly("GPIO19", "F", [(xo, r6g[1]), r6g], 0.20)
    for ref, pin in (("U1", "25"), ("U1", "26"), ("R5", "1"), ("R6", "2"), ("R1", "1"), ("OK3", "4")):
        seed_pad(pads_of(ref, pin)[0])

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            if not try_gnd_via_beside("GND_MCU", p):
                try_gnd_via("GND_MCU", p.x, p.y)
    # U1.51, the module's lower right corner ground pad, sits in a pocket of the front pour
    # closed by GPIO18, GPIO19 and R4's 3V3 feed: it gets its own via to the back pour.
    for ref, pin in (("OK3", "3"), ("U1", "51")):
        p = pads_of(ref, pin)[0]
        if not try_gnd_via_beside("GND_MCU", p):
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    # 0.30 mm, the bus lines at 0.30 mm. Supply trunks are drawn above.
    order = (
        ("VBUS", (0.50, 0.40, 0.30)),
        ("GPIO8", (0.20, 0.15)), ("GPIO9", (0.20, 0.15)),
        ("GPIO18", (0.20, 0.15)), ("GPIO20", (0.20, 0.15)), ("GPIO19", (0.20, 0.15)),
        ("LED_DOOR", (0.20, 0.15)),
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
